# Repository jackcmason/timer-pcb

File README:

The accompanying PCB design for the arduino-timer repository, designed in KiCAD

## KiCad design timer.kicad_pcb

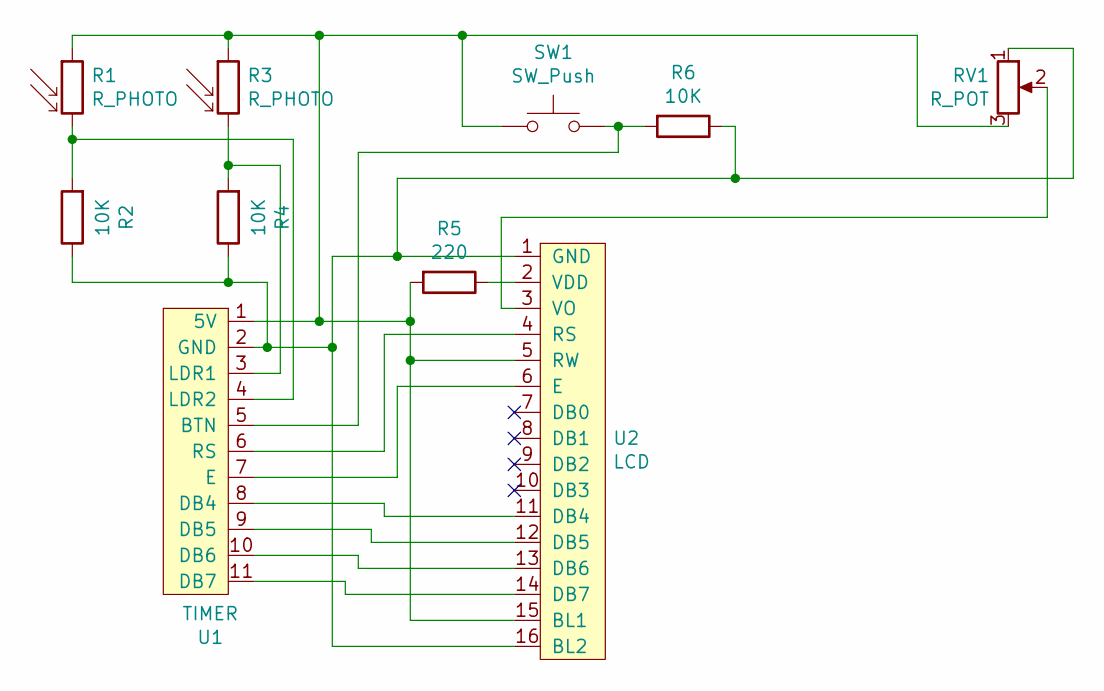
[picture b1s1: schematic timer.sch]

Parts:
R1, R3: R_PHOTO; R_LDR_4.9x4.2mm_P2.54mm_Vertical
R2, R4, R6: 10K; R_Axial_DIN0207_L6.3mm_D2.5mm_P10.16mm_Horizontal
R5: 220; R_Axial_DIN0207_L6.3mm_D2.5mm_P10.16mm_Horizontal
RV1: R_POT; Potentiometer_ACP_CA9-V10_Vertical
SW1: SW_Push; SW_PUSH_6mm
U1: TIMER; TIMER_CONN
U2: LCD; PinSocket_1x16_P2.54mm_Vertical

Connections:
unnamed: R1.1, R3.1, R5.2, RV1.3, SW1.1, U1.1 (5V), U2.5 (RW), U2.15 (BL1)
unnamed: R1.2, R2.2, U1.4 (LDR2)
unnamed: R2.1, R4.1, R6.1, RV1.1, U1.2 (GND), U2.1 (GND), U2.16 (BL2)
unnamed: R3.2, R4.2, U1.3 (LDR1)
unnamed: R5.1, U2.2 (VDD)
unnamed: R6.2, SW1.2, U1.5 (BTN)
unnamed: RV1.2, U2.3 (VO)
unnamed: U1.6 (RS), U2.4 (RS)
unnamed: U1.7 (E), U2.6 (E)
unnamed: U1.8 (DB4), U2.11 (DB4)
unnamed: U1.9 (DB5), U2.12 (DB5)
unnamed: U1.10 (DB6), U2.13 (DB6)
unnamed: U1.11 (DB7), U2.14 (DB7)

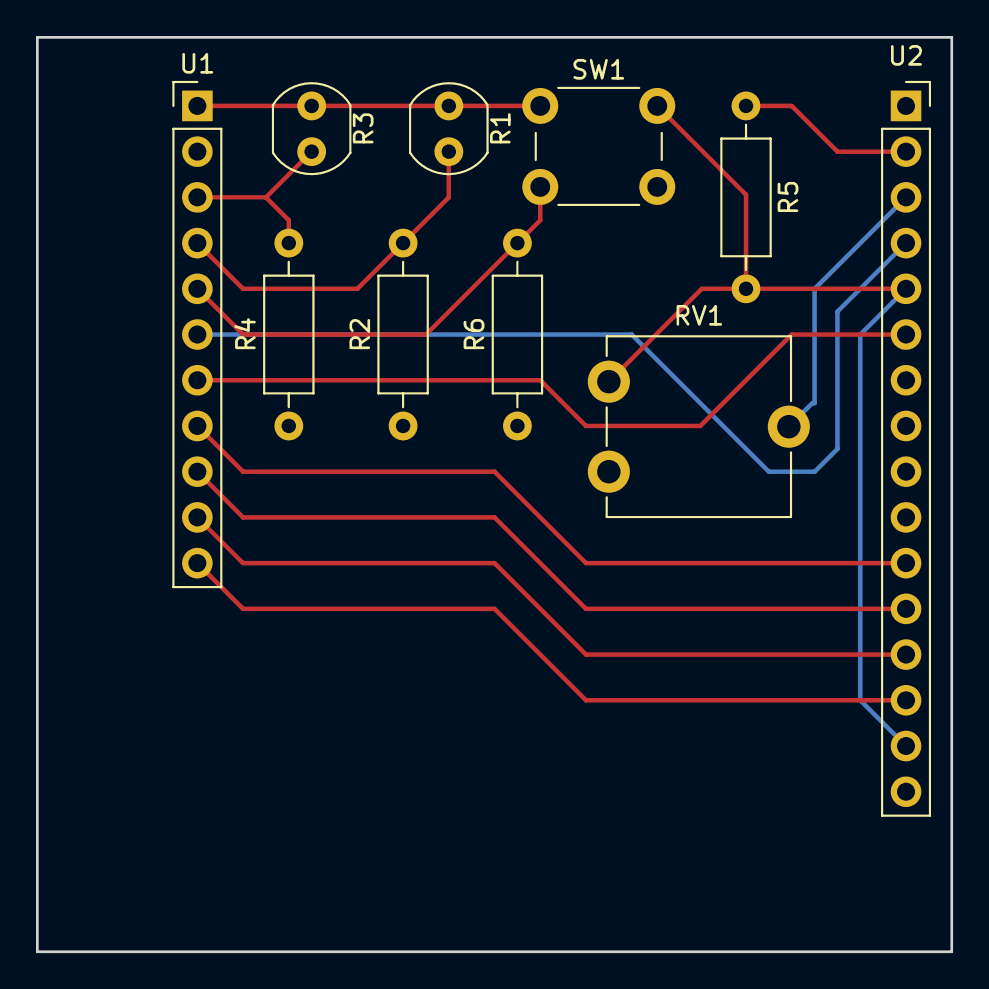
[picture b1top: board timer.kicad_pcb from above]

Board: 2 copper layers, 50.8 x 50.8 mm, 10 parts (0 on the bottom side), 13 nets.

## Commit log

2018-12-10 initial release
2018-12-15 added README
